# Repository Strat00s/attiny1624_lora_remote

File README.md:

# attiny1624_lora_remote
Simple attiny1624 based lora remote (for gate and such)

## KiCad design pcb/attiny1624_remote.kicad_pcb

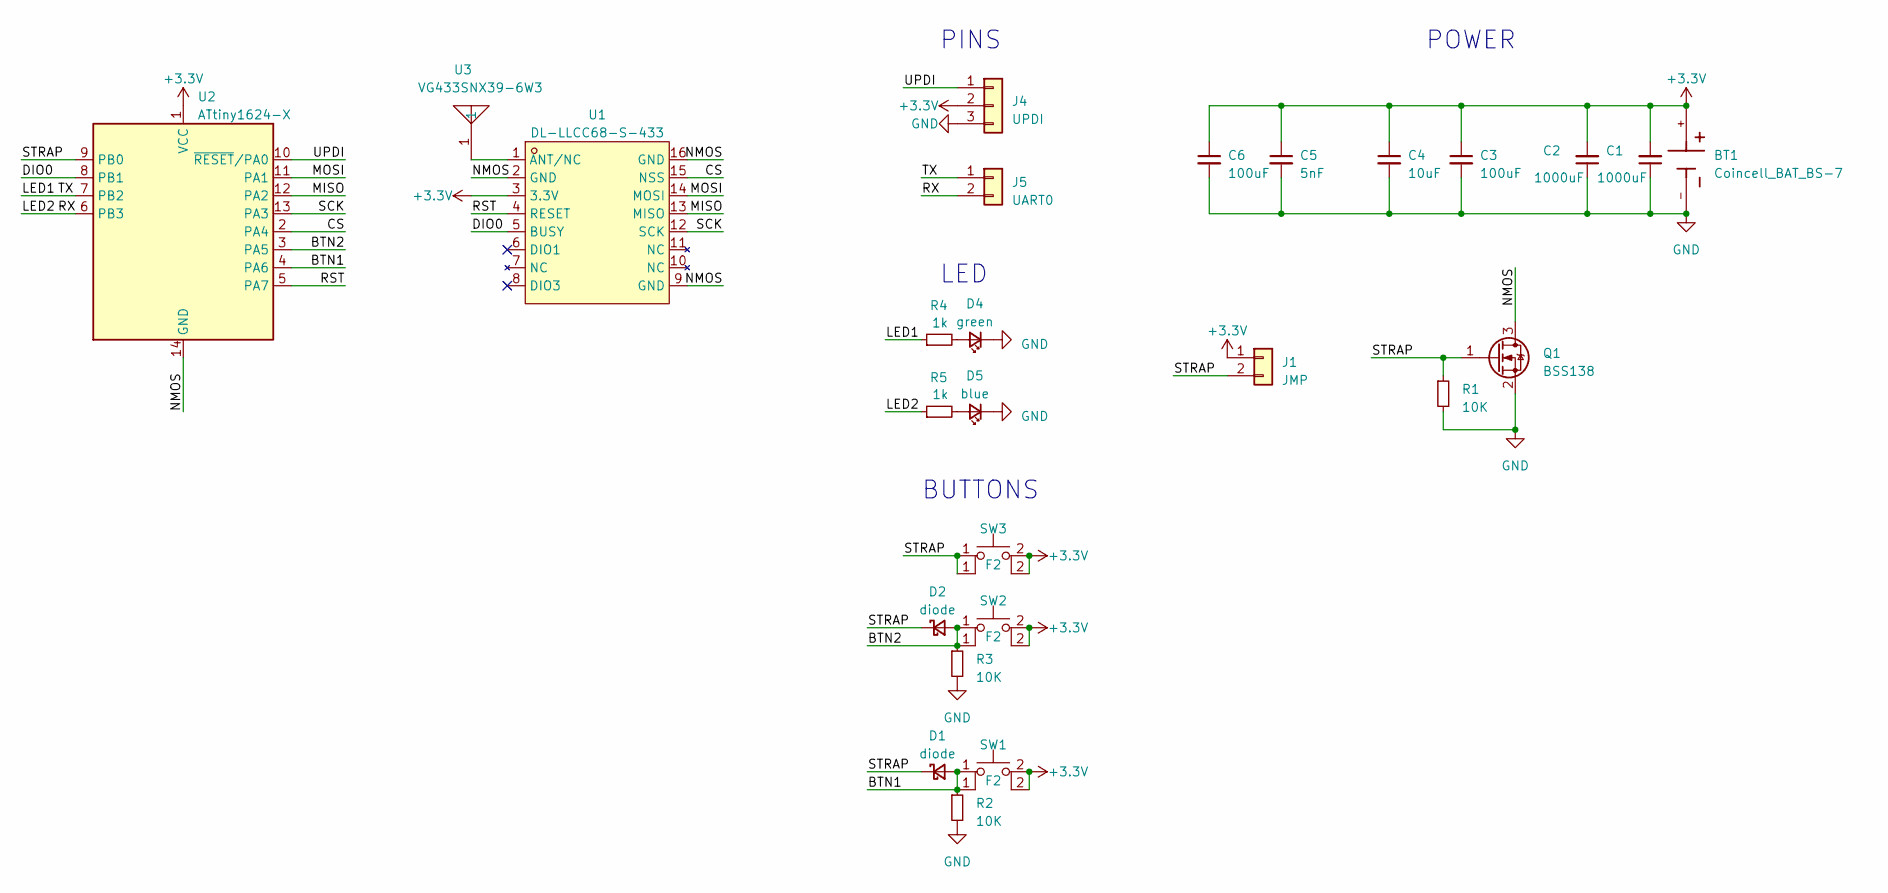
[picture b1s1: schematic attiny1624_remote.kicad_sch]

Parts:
BT1: Coincell_BAT_BS-7; BAT_BS-7; PARTREV H
C1, C2: 1000uF; C_Disc_D8.0mm_W2.5mm_P5.00mm
C3: 100uF; C_0603_1608Metric_Pad1.08x0.95mm_HandSolder
C4: 10uF; C_0603_1608Metric_Pad1.08x0.95mm_HandSolder
C5: 5nF; C_0603_1608Metric_Pad1.08x0.95mm_HandSolder
C6: 100uF; C_0805_2012Metric_Pad1.18x1.45mm_HandSolder
D1, D2: diode; D_SOD-323_HandSoldering
D4: green; LED_0603_1608Metric_Pad1.05x0.95mm_HandSolder
D5: blue; LED_0603_1608Metric_Pad1.05x0.95mm_HandSolder
J1: JMP; PinHeader_1x02_P2.54mm_Vertical
J4: UPDI; PinHeader_1x03_P2.54mm_Vertical
J5: UART0; PinHeader_1x02_P2.54mm_Vertical
Q1: BSS138; SOT-23
R1, R2, R3: 10K; R_0603_1608Metric_Pad0.98x0.95mm_HandSolder
R4, R5: 1k; R_0603_1608Metric_Pad0.98x0.95mm_HandSolder
SW1, SW2, SW3: F2; SW_PUSH_6mm
U1: DL-LLCC68-S-433; Ai-Thinker-Ra-01-LoRa; LCSC Part C2894789
U2: ATtiny1624-X; TSSOP-14_4.4x5mm_P0.65mm
U3: VG433SNX39-6W3; ANT-TH_T14-433M; LCSC Part C718844

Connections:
+3.3V: BT1.+, C1.2, C2.2, C3.1, C4.1, C5.1, C6.1, J1.1, J4.2, SW1.2, SW2.2, SW3.2, U1.3 (3.3V), U2.1 (VCC)
/BTN1: D1.2 (A), R2.1, SW1.1, U2.4 (PA6)
/BTN2: D2.2 (A), R3.1, SW2.1, U2.3 (PA5)
/CS: U1.15 (NSS), U2.2 (PA4)
/DIO0: U1.5 (BUSY), U2.8 (PB1)
/LED1: J5.1, R4.1, U2.7 (PB2)
/LED2: J5.2, R5.1, U2.6 (PB3)
/MISO: U1.13 (MISO), U2.12 (PA2)
/MOSI: U1.14 (MOSI), U2.11 (PA1)
/NMOS: Q1.3 (D), U1.2 (GND), U1.9 (GND), U1.16 (GND), U2.14 (GND)
/RST: U1.4 (RESET), U2.5 (PA7)
/SCK: U1.12 (SCK), U2.13 (PA3)
/STRAP: D1.1 (K), D2.1 (K), J1.2, Q1.1 (G), R1.1, SW3.1, U2.9 (PB0)
/UPDI: J4.1, U2.10 (~RESET/PA0)
GND: BT1.-, C1.1, C2.1, C3.2, C4.2, C5.2, C6.2, D4.1 (K), D5.1 (K), J4.3, Q1.2 (S), R1.2, R2.2, R3.2
unnamed: D4.2 (A), R4.2
unnamed: D5.2 (A), R5.2
unnamed: U1.1 (ANT/NC), U3.1

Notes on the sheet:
LED
PINS
BUTTONS
POWER

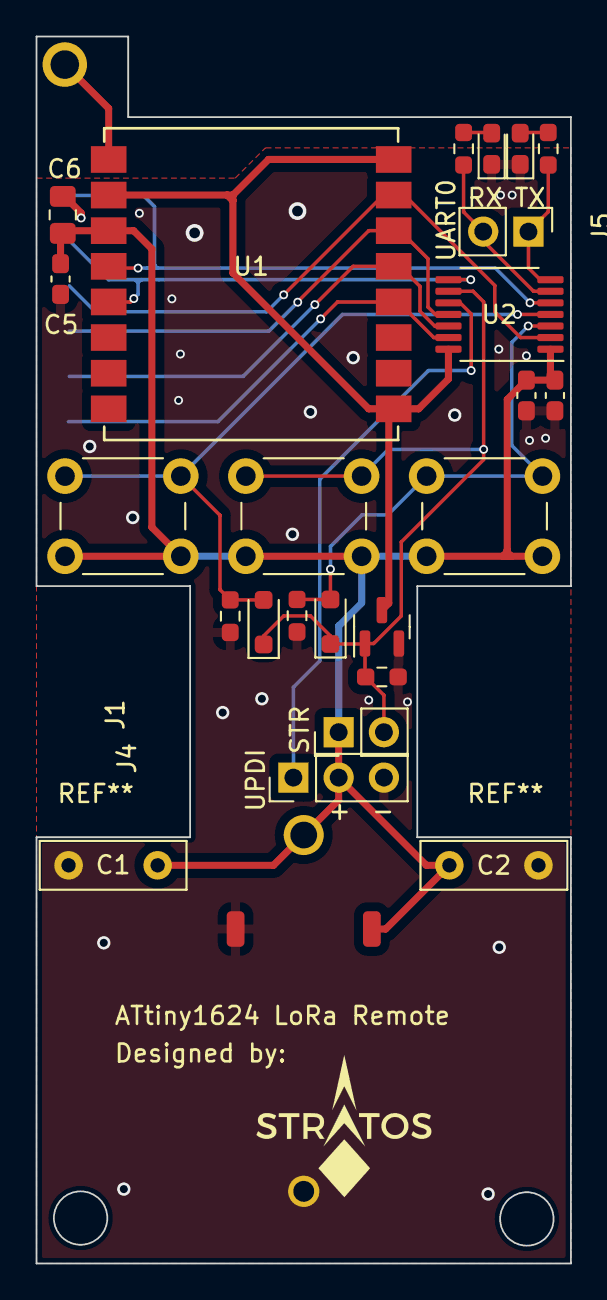
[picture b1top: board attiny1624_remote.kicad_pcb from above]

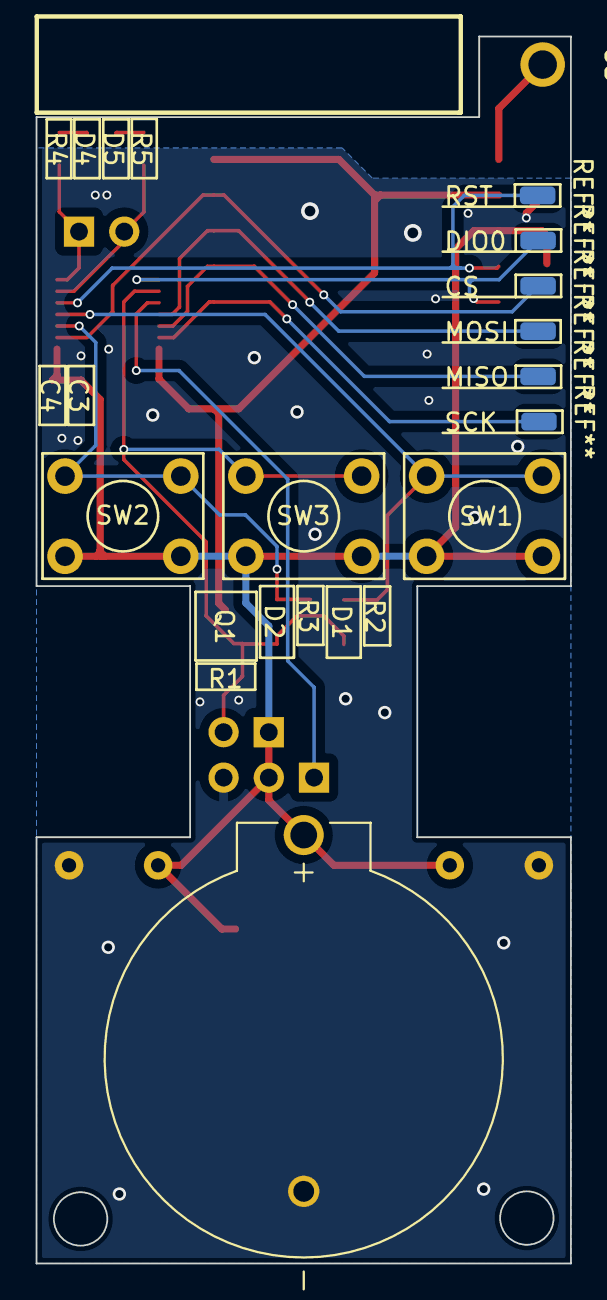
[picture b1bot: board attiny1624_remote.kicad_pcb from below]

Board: 2 copper layers, 30.0 x 68.9 mm, 26 parts (2 on the bottom side), 18 nets.

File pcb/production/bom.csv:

Designator,Footprint,Quantity,Value,LCSC Part #
BT1,BAT_BS-7,1,Coincell_BAT_BS-7,
"C1, C2",C_Disc_D8.0mm_W2.5mm_P5.00mm,2,1000uF,
C3,0603,1,100uF,
C4,0603,1,10uF,
C5,0603,1,5nF,
C6,0805,1,100uF,
"D1, D2",D_SOD-323_HandSoldering,2,diode,
D4,0603,1,green,
D5,0603,1,blue,
J1,PinHeader_1x02_P2.54mm_Vertical,1,JMP,
J4,PinHeader_1x03_P2.54mm_Vertical,1,UPDI,
J5,PinHeader_1x02_P2.54mm_Vertical,1,UART0,
Q1,SOT-23,1,BSS138,
"R1, R2, R3",0603,3,10K,
"R4, R5",0603,2,1k,
"SW1, SW2, SW3",SW_PUSH_6mm,3,F2,
U1,Ai-Thinker-Ra-01-LoRa,1,DL-LLCC68-S-433,C2894789
U2,TSSOP-14_4.4x5mm_P0.65mm,1,ATtiny1624-X,
U3,ANT-TH_T14-433M,1,VG433SNX39-6W3,C718844

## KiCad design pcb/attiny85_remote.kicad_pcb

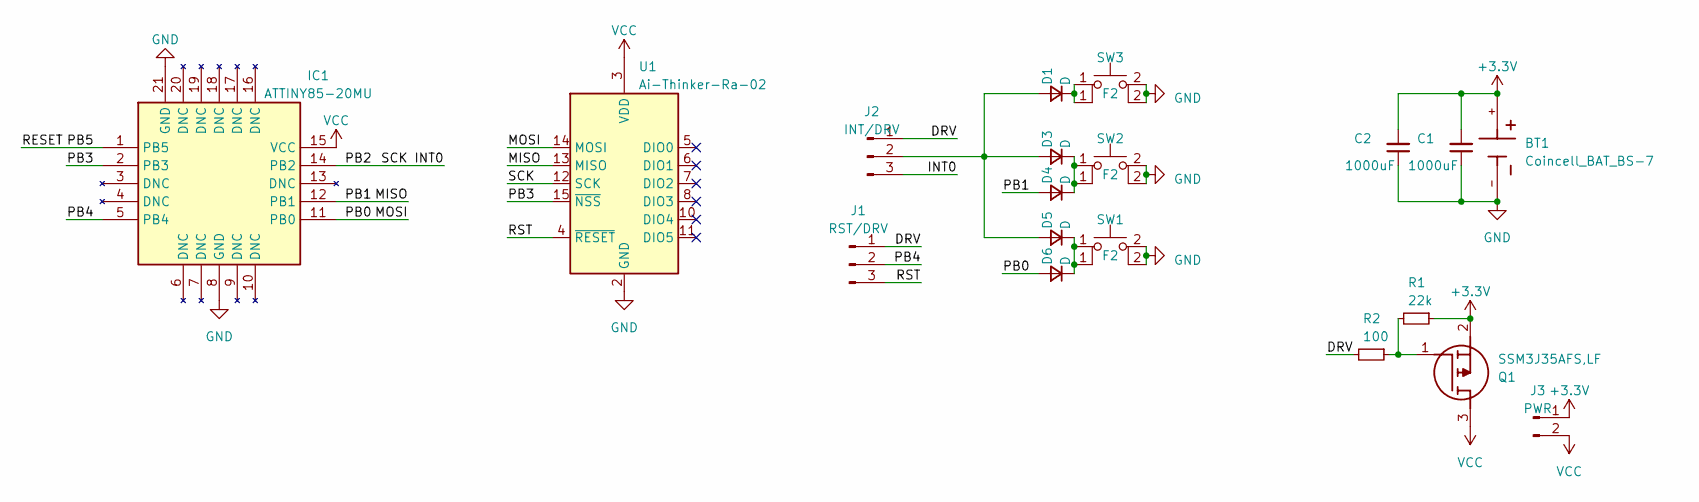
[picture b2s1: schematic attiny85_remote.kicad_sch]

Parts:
BT1: Coincell_BAT_BS-7; BAT_BS-7; PARTREV H
C1, C2: 1000uF; C_Disc_D8.0mm_W2.5mm_P5.00mm
D1, D3, D4, D5, D6: D; D_DO-35_SOD27_P7.62mm_Horizontal
IC1: ATTINY85-20MU; QFN50P400X400X80-21N-D; Mouser Part Number 556-ATTINY85-20MU
J1: RST/DRV; SolderJumper-3_P1.3mm_Open_Pad1.0x1.5mm
J2: INT/DRV; SolderJumper-3_P1.3mm_Open_Pad1.0x1.5mm
J3: PWR; SolderJumper-2_P1.3mm_Open_Pad1.0x1.5mm
Q1: SSM3J35AFS,LF; SSM3J35AFSLF; Mouser Part Number 757-SSM3J35AFSLF
R1: 22k; R_Axial_DIN0207_L6.3mm_D2.5mm_P10.16mm_Horizontal
R2: 100; R_Axial_DIN0207_L6.3mm_D2.5mm_P10.16mm_Horizontal
SW1, SW2, SW3: F2; SW_PUSH_6mm
U1: Ai-Thinker-Ra-02; Ai-Thinker-Ra-01-LoRa

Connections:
+3.3V: BT1.+, C1.2, C2.2, J3.1, Q1.2 (S), R1.1
/DRV: J1.1, J2.1, R2.2
/INT0: IC1.14 (PB2), J2.3, U1.12 (SCK); also elsewhere on the board
/MISO: D4.2 (A), IC1.12 (PB1), U1.13 (MISO); also elsewhere on the board
/MOSI: D6.2 (A), IC1.11 (PB0), U1.14 (MOSI); also elsewhere on the board
/PB3: IC1.2 (PB3), U1.15 (~NSS); also elsewhere on the board
/PB4: IC1.5 (PB4), J1.2; also elsewhere on the board
/RST: J1.3, U1.4 (~RESET)
GND: BT1.-, C1.1, C2.1, IC1.8 (GND), IC1.21 (GND), SW1.2, SW2.2, SW3.2, U1.1 (GND), U1.2 (GND), U1.9 (GND), U1.16 (GND); also elsewhere on the board
unnamed: D1.2 (A), D3.2 (A), D5.2 (A), J2.2
unnamed: D1.1 (K), SW3.1
unnamed: D3.1 (K), D4.1 (K), SW2.1
unnamed: D5.1 (K), D6.1 (K), SW1.1
unnamed: Q1.1 (G), R1.2, R2.1
VCC: IC1.15 (VCC), J3.2, Q1.3 (D), U1.3 (VDD); also elsewhere on the board

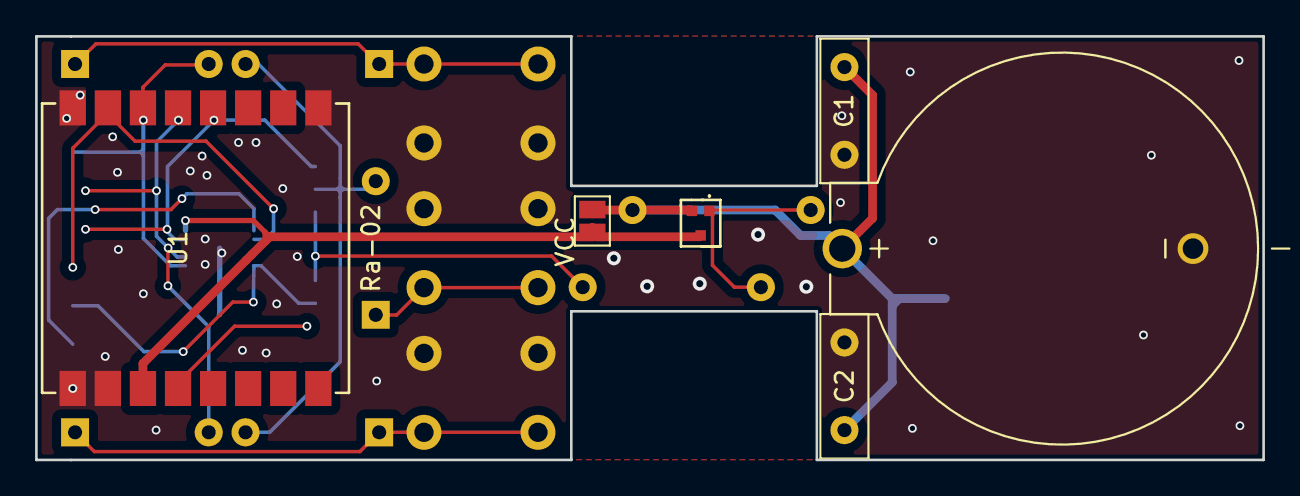
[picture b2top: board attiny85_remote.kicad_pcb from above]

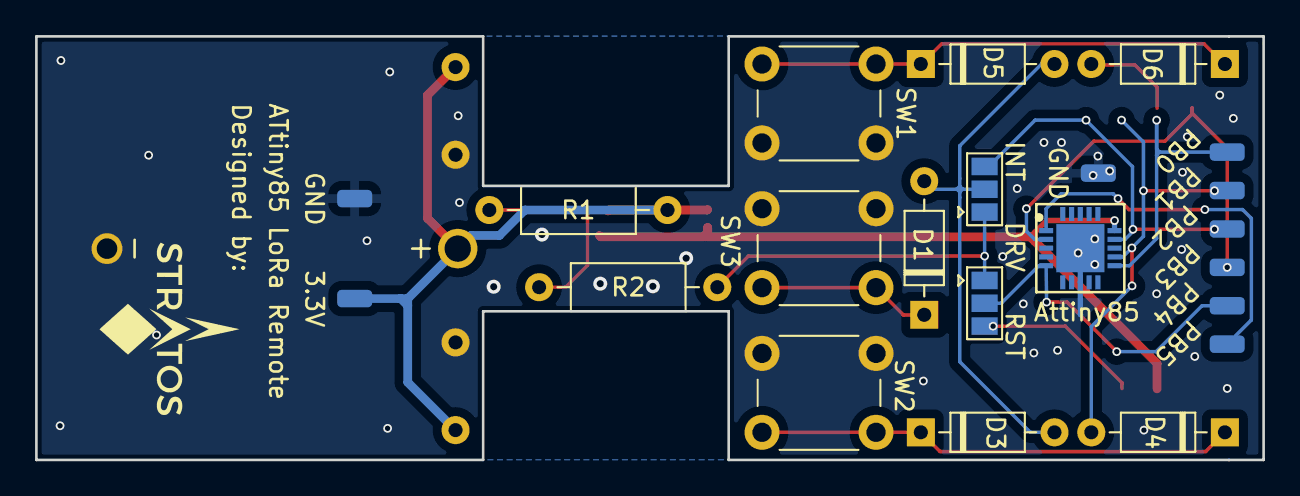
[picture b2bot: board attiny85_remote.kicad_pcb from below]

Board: 2 copper layers, 70.0 x 24.2 mm, 19 parts (13 on the bottom side), 15 nets.

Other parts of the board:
Attiny85: ATTINY85-20MU; QFN50P400X400X80-21N-D

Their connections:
/INT0: Attiny85.14 (PB2); also elsewhere on the board
/MISO: Attiny85.12 (PB1); also elsewhere on the board
/MOSI: Attiny85.11 (PB0); also elsewhere on the board
/PB3: Attiny85.2 (PB3); also elsewhere on the board
/PB4: Attiny85.5 (PB4); also elsewhere on the board
GND: Attiny85.8 (GND), Attiny85.21 (GND); also elsewhere on the board
VCC: Attiny85.15 (VCC); also elsewhere on the board

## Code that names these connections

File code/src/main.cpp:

/** @file main.cpp
 * @author Lukáš Baštýř (l.bastyr@seznam.cz, 492875)
 * @brief Simple remote based around Attiny1624 and LoRa SX1278 using TinyMesh.
 * @version 0.1
 * @date 27-11-2023
 * 
 * @copyright Copyright (c) 2023
 * 
 */

#include <Arduino.h>
#include <SPI.h>
#include <avr/wdt.h>
#include "libs/interfaces/sx127xInterfaceWrapper.hpp"
#include "libs/sx127x.hpp"
#include "libs/tinyMesh.hpp"


#define MOSI PIN_PA1
#define MISO PIN_PA2
#define SCK  PIN_PA3
#define CS   PIN_PA4
#define RST  PIN_PA7
#define DIO0 PIN_PB1

#define STRAP PIN_PB0

#define LED_R PIN_PB2
#define LED_B PIN_PB3

#define BTN1 PIN_PA6
#define BTN2 PIN_PA5
#define BTN3 STRAP


#define BTN1_PORT 16
#define BTN2_PORT 32
#define BTN3_PORT 198


/*----(FUNCTION MACROS)----*/
#define IF_X_FALSE(x, msg, cmd) {if (x) {Serial.println(msg); cmd;}}
#define IF_X_TRUE(x, msg, cmd)  {if (x) {Serial.print(msg); Serial.print(x, 2); Serial.print(" ("); Serial.print(x); Serial.println(")"); cmd;}}
//reset the mcu
#define RESET() {Serial.println("reseting"); wdt_enable(WDTO_15MS); while (true);}


TinyMesh tm(TM_NODE_TYPE_LP_NODE);
SX127X lora(CS, RST, DIO0);
sx127xInterfaceWrapper lora_if(&lora);
packet_t packet;


/*----(SX127X CALLBACKS)----*/
void SPIBeginTransfer() {
    SPI.beginTransaction({14000000, MSBFIRST, SPI_MODE0});
}
void SPIEndTransfer() {
    SPI.endTransaction();
}
void SPITransfer(uint8_t addr, uint8_t *buffer, size_t length) {
    SPI.transfer(addr);
    SPI.transfer(buffer, length);
}


/*----(HELPERS & OTHER)----*/
void failed() {
    while(true) {
        digitalWrite(LED_B, HIGH);
        digitalWrite(LED_R, LOW);
        delay(200);
        digitalWrite(LED_B, LOW);
        digitalWrite(LED_R, HIGH);
        delay(200);
    }
}

void printPacket() {
    Serial.print("Version:             ");
    Serial.println(packet.fields.version);
    Serial.print("Device type:         ");
    Serial.println(tm.getBits(packet.fields.flags, TM_NODE_TYPE_MSB, TM_NODE_TYPE_LSB));
    Serial.print("Message id:          ");
    Serial.println(tm.getMessageId(&packet));
    Serial.print("Repeate count:       ");
    Serial.println(tm.getBits(packet.fields.flags, TM_RPT_CNT_MSB, TM_RPT_CNT_LSB));
    Serial.print("Source address:      ");
    Serial.println(packet.fields.source);
    Serial.print("Destination address: ");
    Serial.println(packet.fields.destination);
    Serial.print("Message type:        ");
    Serial.println(tm.getBits(packet.fields.flags, TM_MSG_TYPE_MSB, TM_MSG_TYPE_LSB));
    Serial.print("Data length:         ");
    Serial.println(packet.fields.data_length);
    Serial.print("Data: ");
    for (int i = 0; i < packet.fields.data_length; i++) {
        Serial.print(packet.fields.data[i]);
        Serial.print(" ");
    }
    Serial.println();
}


/** @brief Handler for incoming packets (not used)
 * 
 */
void handleIncomingAnswer() {
    uint8_t msg_type = tm.getBits(packet.fields.flags, TM_MSG_TYPE_MSB, TM_MSG_TYPE_LSB);
    if (msg_type == TM_MSG_OK) {
        Serial.println("OK Answer");
        return;
    }

    if (msg_type == TM_MSG_ERR) {
        Serial.println("ERR Answer");
        return;
    }

    if (msg_type == TM_MSG_CUSTOM) {
        Serial.println("Custom Answer");
        return;
    }
}

/** @brief Send packet on our only interface and save it's ID
 * 
 * @return 0 on success, errors that occured during transmission
 */
uint8_t sendPacketOnInterface() {
    return lora_if.transmitData(packet.raw, TM_HEADER_LENGTH + packet.fields.data_length);
}

/** @brief Get data from interface and try to build a pakcet
 * 
 * @return 0 on success, lora or tm errors on failure
 */
uint8_t getPacketOnInterface() {
    uint8_t ret = 0;
    uint8_t len;
    ret = lora_if.getData(packet.raw, &len);
    if (ret) return ret;

    //check if packet is valid
    ret = tm.checkHeader(&packet);
    return ret;
}


/** @brief Blocking send and receive function. Exits once either answer is received or timeout/error occured enough times.
 * 
 * @param destination Destionation to which to send the packet
 * @param message_type Message type
 * @param buffer Buffer containing data to be sent
 * @param length Length of data
 * @param timeout Timeout (ms) when waiting for answer
 * @return 
 */
uint8_t requestAwait(uint8_t destination, uint8_t message_type, uint8_t *buffer, uint8_t length, uint32_t timeout = 1000) {
    uint8_t ret = 0;
    uint16_t msg_id = tm.lcg();

    for (int i = 0; i < TM_MAX_REPEAT + 1; i++) {
        ret = tm.buildPacket(&packet, destination, msg_id, message_type, buffer, length, i);
        Serial.print("build packet: ");
        Serial.println(ret);
        IF_X_TRUE(ret, "Failed to build packet: ", continue);

        sendPacketOnInterface();

        //start reception on lora
        ret = lora_if.startReception();
        IF_X_TRUE(ret, "Failed to start reception: ", continue);

        //timeout return value
        ret = 0xFF;

        //wait for response
        auto timer = millis();
        while (millis() - timer < timeout) {
            //got some data
            if (digitalRead(DIO0)) {
                ret = getPacketOnInterface();
                IF_X_TRUE(ret, "failed to get packet: ", continue);

                ret = tm.checkPacket(&packet);
                Serial.println(ret);
                IF_X_TRUE((ret & TM_PACKET_RESPONSE) == 0, "not an answer: ", continue);
                Serial.println("Incoming packet is an answer");
                return 0;
            }
        }
        //tm.clearSentQueue();
    }

    return ret;
}


void setup() {
    //Run at 5MHz
    //_PROTECTED_WRITE(CLKCTRL.MCLKCTRLB, CLKCTRL_PEN_bm);    //enable prescaler
    _PROTECTED_WRITE(CLKCTRL.MCLKCTRLB, CLKCTRL_PDIV_4X_gc | CLKCTRL_PEN_bm);   //set prescaler to 4 -> 5MHz
    _PROTECTED_WRITE(CLKCTRL.MCLKCTRLA, CLKCTRL_CLKSEL_OSC20M_gc);  //set oscilator to 20MHz

    //configure pins
    pinMode(LED_R, OUTPUT);
    pinMode(LED_B, OUTPUT);
    pinMode(BTN1, INPUT);
    pinMode(BTN2, INPUT);
    pinMode(BTN3, INPUT);

    //SPI init
    SPI.begin();

    //LORA init
    lora.registerSPIBeginTransfer(SPIBeginTransfer);
    lora.registerSPIEndTransfer(SPIEndTransfer);
    lora.registerSPITransfer(SPITransfer);
    lora.reset();
    uint16_t ret = lora.begin(868.0, 0x24, 8, LORA_BANDWIDTH_125kHz, LORA_SPREADING_FACTOR_9, LORA_CODING_RATE_4_7);
    //IF_X_TRUE(ret, "lora begin failed: ", failed());
    if(ret) failed();

    //TinyMesh init
    tm.setSeed(46290);
    tm.setAddress(23);

    //1. register
    digitalWrite(LED_B, HIGH);
    ret = requestAwait(tm.getGatewayAddress(), TM_MSG_REGISTER, nullptr, 0, 1000);
    if (ret) failed();
    digitalWrite(LED_B, LOW);

    //save data from registration (our address is premade)
    tm.clearSentQueue();
    tm.setGatewayAddress(packet.fields.source);

    digitalWrite(LED_R, LOW);
}


bool pressed = false;
uint16_t ret = 0;
void loop() {

    //wake up
    //our service request routine
    if ((digitalRead(BTN1) || digitalRead(BTN2) || digitalRead(BTN3)) && !pressed) {
        pressed = true;
        digitalWrite(LED_B, HIGH);
        digitalWrite(LED_R, HIGH);

        //send custom empty message on specified button port to address 46
        if (digitalRead(BTN1)) {
            uint8_t data = 'T';
            ret = requestAwait(46, TM_MSG_CUSTOM, &data, 1);
        }
        else if (digitalRead(BTN2))
            ret = requestAwait(46, TM_MSG_CUSTOM, nullptr, 0);
        else if (digitalRead(BTN3)) {
            uint8_t data[] = {'N', 'D', 'B', 3, 7, 'T', 21,35, 'H', 36, 83};
            ret = requestAwait(tm.getGatewayAddress(), TM_MSG_CUSTOM, data, 11);
        }

        //blue on success, red on error
        if (ret || tm.getBits(packet.fields.flags, TM_MSG_TYPE_MSB, TM_MSG_TYPE_LSB) != TM_MSG_OK)
            digitalWrite(LED_B, LOW);
        else
            digitalWrite(LED_R, LOW);

        delay(500);

        digitalWrite(LED_R, LOW);
        digitalWrite(LED_B, LOW);
    }

    //reset pressed state
    if (!digitalRead(BTN1) && !digitalRead(BTN2) && !digitalRead(BTN3) && pressed)
        pressed = false;

    tm.clearSentQueue();
}

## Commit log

2023-07-03 before rework
2023-07-04 rework done
2023-07-04 gerber out
2023-07-19 done
2023-07-27 kikit tabs
2023-07-27 fill
2023-08-11 move to attiny1624
2023-08-12 pcb done?
2023-11-25 copy of relay
2023-11-25 platformio project init
2023-11-26 tm update, simple send done
2023-11-27 it works, don't touch it
2024-01-03 big rework
2024-01-04 last big rework for quite some time
2024-01-04 minor update
2024-01-17 rework
2024-01-17 final changes
